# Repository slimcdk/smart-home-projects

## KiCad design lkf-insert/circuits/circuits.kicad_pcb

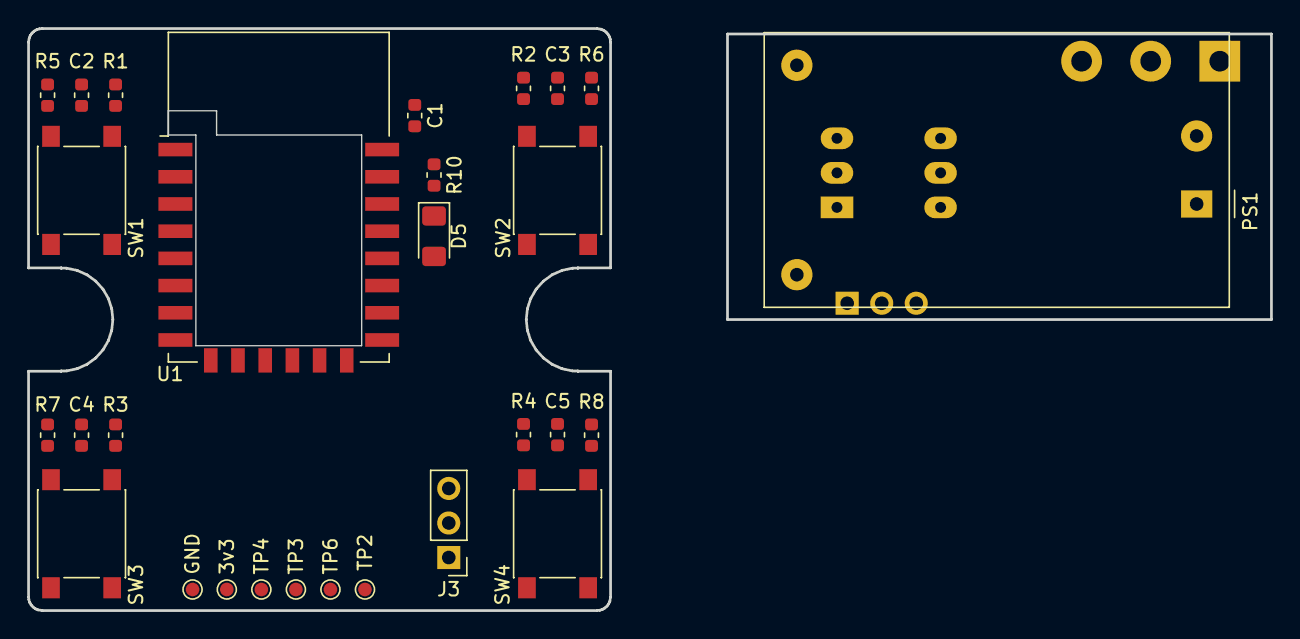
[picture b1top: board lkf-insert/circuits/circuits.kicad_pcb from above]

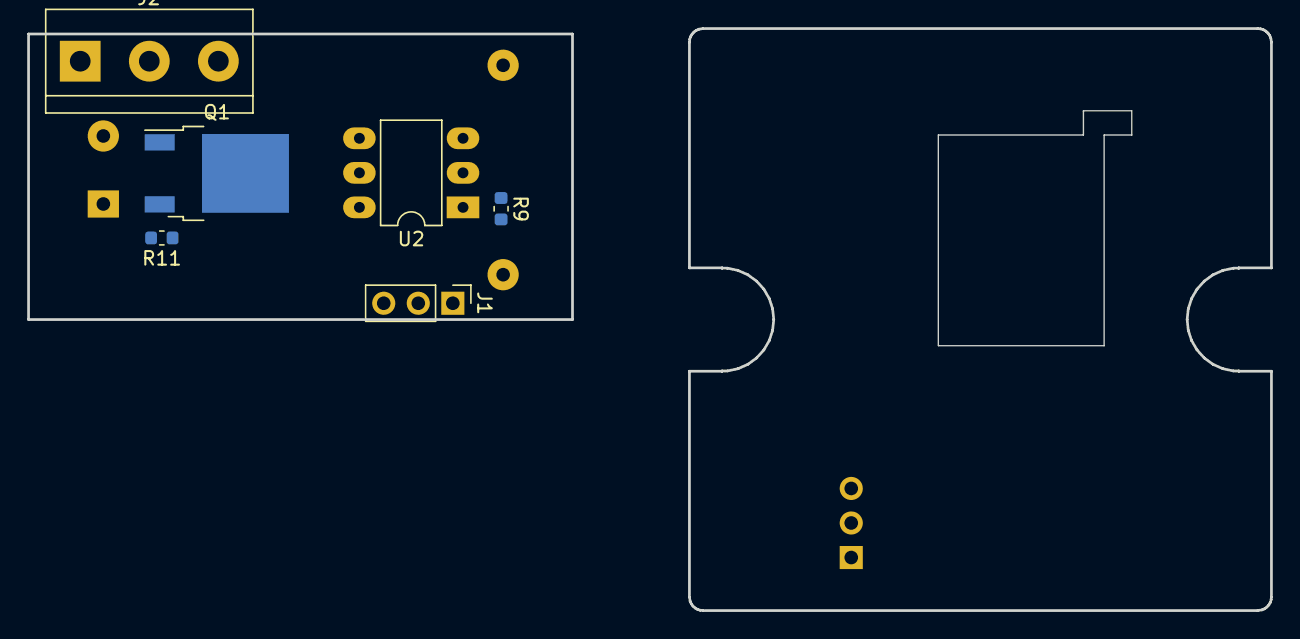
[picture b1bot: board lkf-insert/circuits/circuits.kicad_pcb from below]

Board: 2 copper layers, 91.4 x 42.8 mm, 34 parts (6 on the bottom side), 26 nets, no tracks yet.

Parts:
3v3: TestPoint; TestPoint_Pad_D1.0mm
C1: 10µF; C_0603_1608Metric
C2, C3, C4, C5: 0.1µF; C_0603_1608Metric
D5: LED; LED_1206_3216Metric_Pad1.42x1.75mm_HandSolder
GND: TestPoint; TestPoint_Pad_D1.0mm
J1: BACK_PCB; PinHeader_1x03_P2.54mm_Vertical
J2: AC MAINS CONN; TerminalBlock_bornier-3_P5.08mm
J3: FRONT_PCB; PinHeader_1x03_P2.54mm_Vertical
PS1: HLK-PM03; Converter_ACDC_HiLink_HLK-PMxx
Q1: BT136-500; TO-252-2
R1, R2, R3, R4: 1K; R_0603_1608Metric
R5, R6, R7, R8, R10: 10K; R_0603_1608Metric
R9: 430R; R_0603_1608Metric
R11: 330R; R_0603_1608Metric
SW1, SW2, SW3, SW4: SW_Push; SW_Push_1P1T_NO_6x6mm_H9.5mm
TP2, TP3, TP4, TP6: TestPoint; TestPoint_Pad_D1.0mm
U1: ESP-WROOM-02; ESP-12E-Cutout
U2: MOC3033M; DIP-6_W7.62mm_LongPads

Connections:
+3V3: 3v3.1, C1.1, J3.2, SW1.1, SW2.1, SW3.1, SW4.1, U1.1
/AC_PWR_SIG: J3.1, U1.17
/SW1: C2.2, R1.1, R5.1, U1.7
/SW2: C3.2, R2.1, R6.1, U1.10
/SW3: C4.2, R3.1, R7.1, U1.14
/SW4: C5.2, R4.1, R8.1, U1.4
GND: C1.2, C2.1, C3.1, C4.1, C5.1, GND.1, J3.3, R5.2, R6.2, R7.2, R8.2, R10.2, U1.9, U1.13, U1.18, U1.19
unnamed: D5.1, R10.1
unnamed: D5.2, U1.5
unnamed: J1.1, PS1.3, U2.2
unnamed: J1.2, PS1.4
unnamed: J1.3, R9.2
unnamed: J2.1, PS1.2
unnamed: J2.2, PS1.1, Q1.1
unnamed: J2.3, Q1.2, U2.6
unnamed: Q1.3, R11.1
unnamed: R1.2, SW2.2
unnamed: R2.2, SW1.2
unnamed: R3.2, SW3.2
unnamed: R4.2, SW4.2
unnamed: R9.1, U2.1
unnamed: R11.2, U2.4
unnamed: TP2.1, U1.15
unnamed: TP3.1, U1.11
unnamed: TP4.1, U1.12
unnamed: TP6.1, U1.8

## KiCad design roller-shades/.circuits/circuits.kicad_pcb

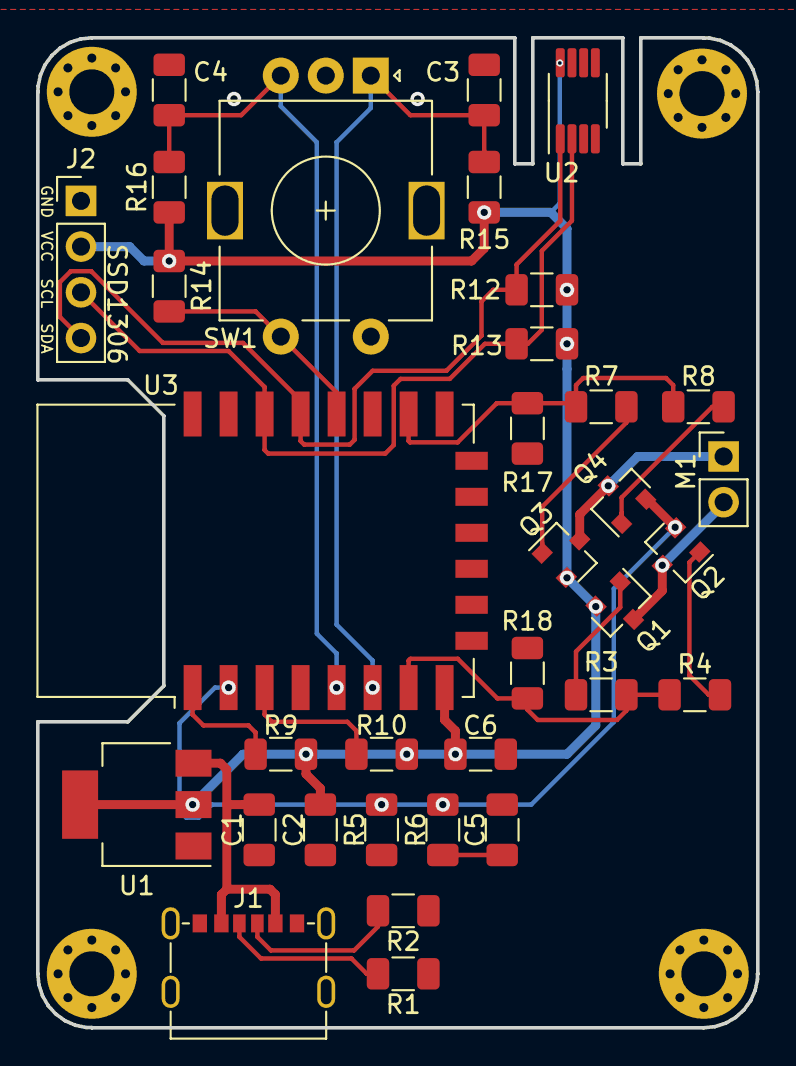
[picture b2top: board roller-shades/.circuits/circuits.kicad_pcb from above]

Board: 2 copper layers, 40.0 x 55.0 mm, 34 parts (0 on the bottom side), 22 nets.

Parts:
C1: 10µF; C_1206_3216Metric
C2: 22µF; C_1206_3216Metric
C3, C4: 10nF; C_1206_3216Metric
C5: 100p; C_1206_3216Metric
C6: 100nF; C_1206_3216Metric
J1: USB_C_Receptacle_USB2.0; USB_C_Receptacle_SHOU_HAN_6P
J2: SSD1306 connector; PinHeader_1x04_P2.54mm_Vertical
M1: Motor_DC; PinHeader_1x02_P2.54mm_Vertical
Q1, Q3: BC807; SOT-23
Q2, Q4: BC817; SOT-23
R1, R2: 5K1; C_1206_3216Metric
R3, R4, R6, R7, R8: 1K; C_1206_3216Metric
R5: 20mR; C_1206_3216Metric
R9, R10, R12, R13, R14, R15, R16, R17, R18: 10K; C_1206_3216Metric
SW1: Rotary_Encoder_Switch; RotaryEncoder_Alps_EC11E-Switch_Vertical_H20mm
U1: AMS1117-3.3; SOT-223-3_TabPin2
U2: MCP9804_MSOP; MSOP-8_3x3mm_P0.65mm
U3: ESP-12F; ESP-12E

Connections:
+3V3: C2.1, C6.1, J2.2, Q1.2, Q3.2, R9.1, R10.1, R12.1, R13.1, R14.1, R15.1, R16.1, U1.2, U2.8, U3.8
+5V: C1.1, J1.A9, J1.B9, U1.3
/ESP_ADC: Q2.2, Q4.2, R5.2, R6.1, U3.2
/ESP_EN: R10.2, U3.3
/ESP_IO0: R14.2, SW1.S1, U3.18
/ESP_IO4: J2.4, R12.2, U2.1, U3.19
/ESP_IO5: J2.3, R13.2, U2.2, U3.20
/ESP_IO12: C3.1, R15.2, SW1.A, U3.6
/ESP_IO13: R3.2, R4.2, R18.2, U3.7
/ESP_IO14: C4.1, R16.2, SW1.B, U3.5
/ESP_IO15: R7.1, R8.1, R17.2, U3.16
/ESP_RST: R9.2, U3.1
GND: C1.2, C2.2, C3.2, C4.2, C5.2, C6.2, J1.A12, J1.B12, J1.S1, J2.1, R1.2, R2.2, R5.1, R17.1, R18.1, SW1.C, SW1.S2, U1.1, U2.4, U3.15
unnamed: C5.1, R6.2
unnamed: J1.A5, R1.1
unnamed: J1.B5, R2.1
unnamed: M1.1, Q3.3, Q4.3
unnamed: M1.2, Q1.3, Q2.3
unnamed: Q1.1, R3.1
unnamed: Q2.1, R4.1
unnamed: Q3.1, R7.2
unnamed: Q4.1, R8.2

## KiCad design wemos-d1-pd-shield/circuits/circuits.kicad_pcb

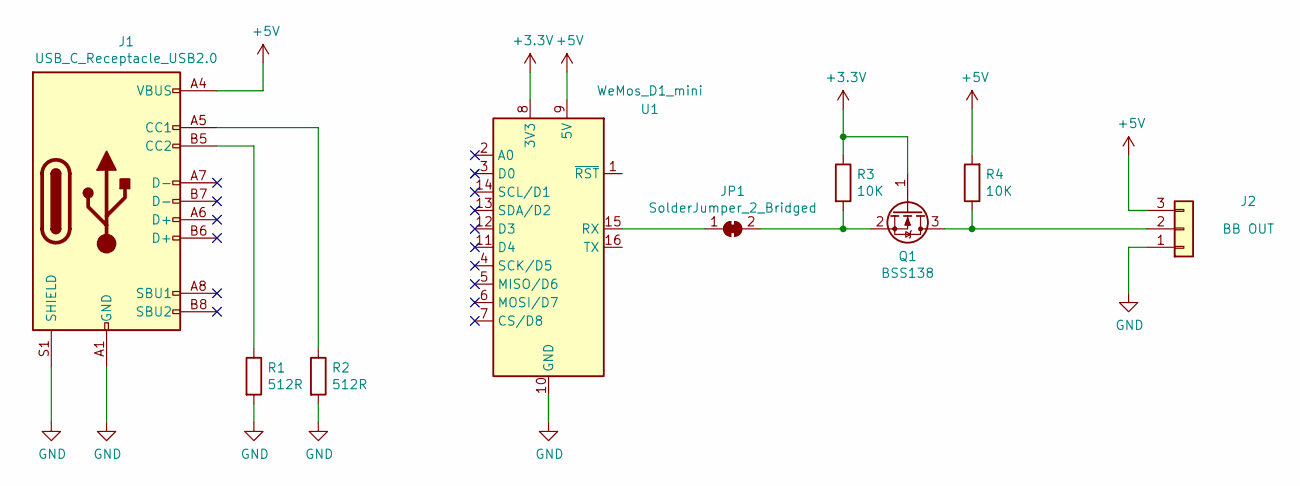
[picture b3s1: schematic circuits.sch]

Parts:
J1: USB_C_Receptacle_USB2.0; USB_C_Receptacle_Palconn_UTC16-G
J2: BB OUT; PinHeader_1x03_P2.54mm_Vertical
JP1: SolderJumper_2_Bridged; SolderJumper-2_P1.3mm_Bridged_Pad1.0x1.5mm
Q1: BSS138; SOT-23
R1, R2: 512R; R_0805_2012Metric
R3, R4: 10K; R_0805_2012Metric
U1: WeMos_D1_mini; WEMOS_D1_mini_light

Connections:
+3V3: Q1.1 (G), R3.1, U1.8 (3V3)
+5V: J1.A4 (VBUS), J1.A9 (VBUS), J1.B4 (VBUS), J1.B9 (VBUS), J2.3, R4.2, U1.9 (5V)
GND: J1.A1 (GND), J1.A12 (GND), J1.B1 (GND), J1.B12 (GND), J1.S1 (SHIELD), J2.1, R1.2, R2.2, U1.10 (GND)
unnamed: J1.A5 (CC1), R2.1
unnamed: J1.B5 (CC2), R1.1
unnamed: J2.2, Q1.3 (D), R4.1
unnamed: JP1.1 (A), U1.15 (RX)
unnamed: JP1.2 (B), Q1.2 (S), R3.2

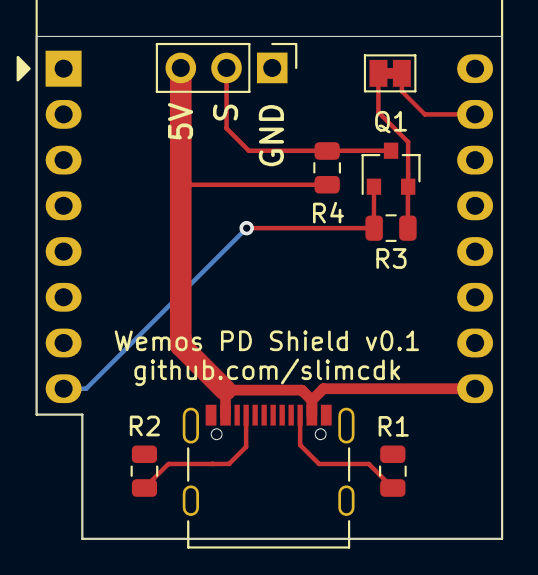
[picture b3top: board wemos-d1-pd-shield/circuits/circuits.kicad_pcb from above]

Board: 2 copper layers, 25.8 x 27.9 mm, 9 parts (0 on the bottom side), 8 nets.
